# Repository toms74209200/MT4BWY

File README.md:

# May the 4 be with you
[4 Pack](https://www.40percent.club/2017/07/4-pack.html) like 4 key macropad

- 4 key macro keyboard
- Cherry MX/Kailh Choc/Kailh Choc V2 key switch compatible
- USB type-C interface
- On-Board CPU(ATmega32U4)

## Reference

This keyboard is inspired by "4 pack".

[Misc/4pack at master · di0ib/Misc](https://github.com/di0ib/Misc/tree/master/4pack)  
https://github.com/di0ib/Misc/tree/master/4pack

[40% Keyboards: 4 Pack](https://www.40percent.club/2017/07/4-pack.html)  
https://www.40percent.club/2017/07/4-pack.html

## License

MIT License

## Author

[toms74209200](<https://github.com/toms74209200>)

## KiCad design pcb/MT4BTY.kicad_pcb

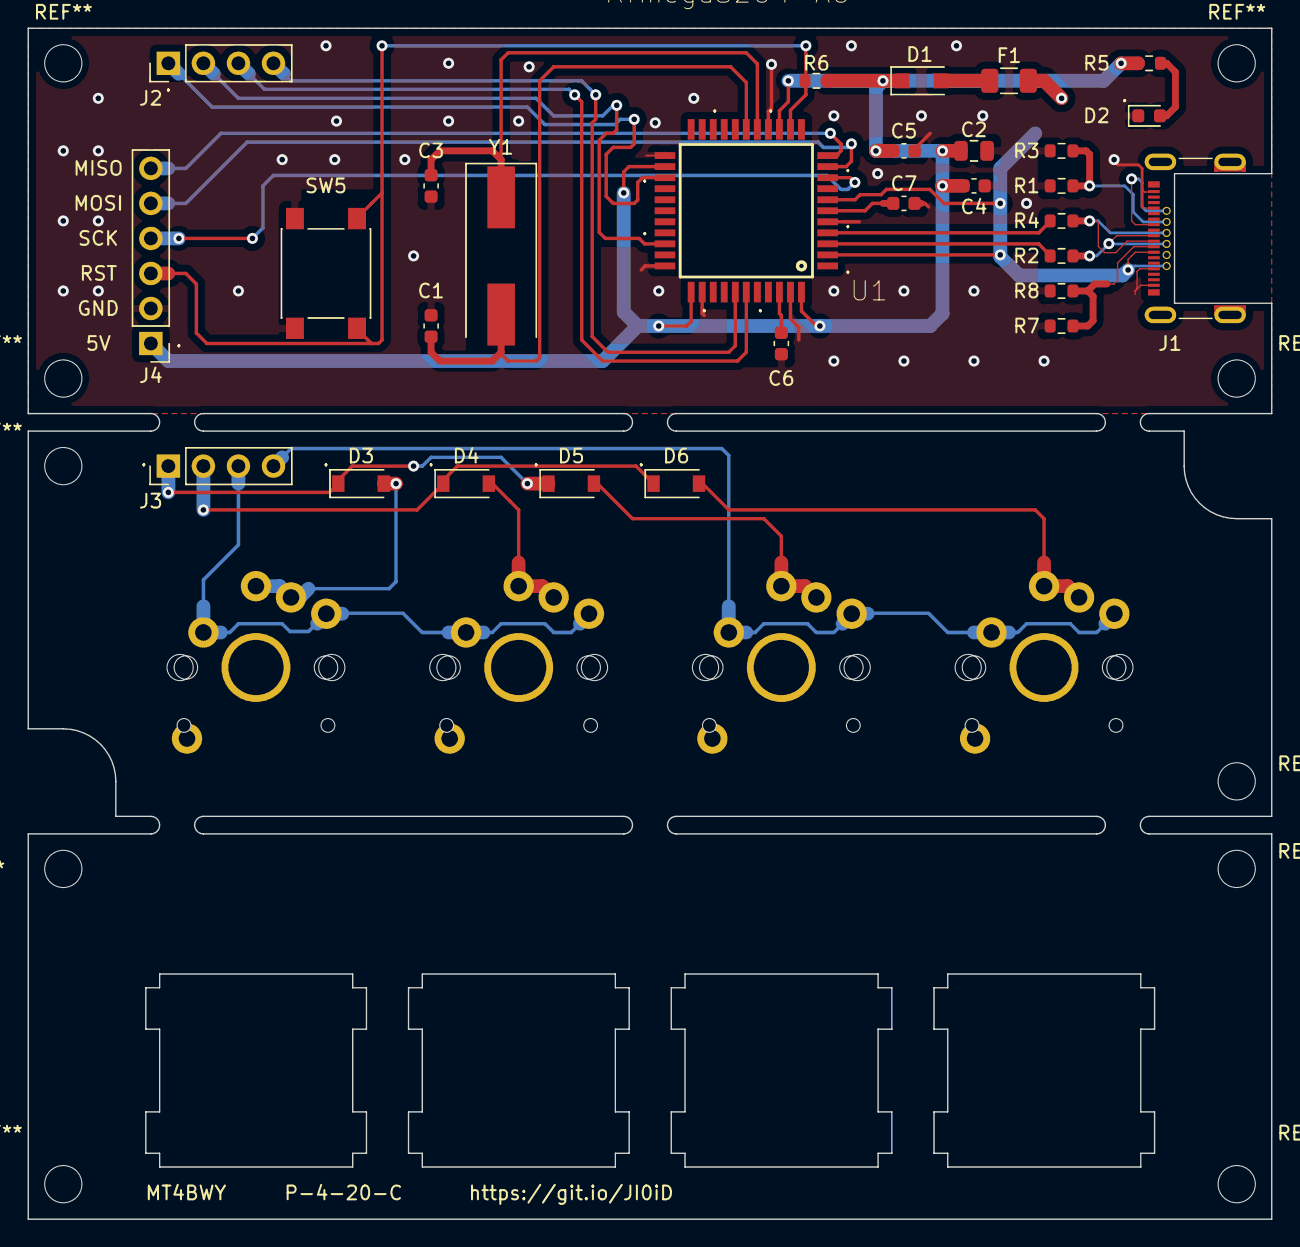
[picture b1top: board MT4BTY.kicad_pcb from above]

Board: 2 copper layers, 90.2 x 86.4 mm, 33 parts (0 on the bottom side), 31 nets.

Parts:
C1, C3: 22p; C_0603_1608Metric
C2: 10u; C_0805_2012Metric
C4, C7: 1u; C_0603_1608Metric
C5, C6: 0.1u; C_0603_1608Metric
D1: RB161MM-20; D_SOD-123F
D2: SMLE13WBC8W1; LED_0603_1608Metric
D3, D4, D5, D6: 1N4148W; D_SOD-123
F1: NANOSMDC050F/13.2; Fuse_1206_3216Metric
J1: CX70M-24P1; USB-C_Female_CX70M-24P1
J2, J3: Conn_01x04_Male; PinHeader_1x04_P2.54mm_Vertical
J4: Conn_01x06_Female; PinHeader_1x06_P2.54mm_Vertical
R1, R3, R5, R6, R7, R8: 10k; R_0603_1608Metric
R2, R4: 22; R_0603_1608Metric
SW1, SW2, SW3, SW4: SW_Push; CherryMX_Choc_V2_1u
SW5: SW_Push; SW_SPST_PTS645
U1: ATmega32U4-AU; ATMEGA32U4-AU
Y1: 16MHz; Crystal_SMD_HC49-SD

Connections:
+5V: C2.1, C4.1, C5.1, D1.1, J4.1, R5.1, R6.1, U1.14, U1.24, U1.34, U1.44
/A2: J2.4, U1.38
/A3: J2.3, U1.39
/CPU_ROW0: J2.1, U1.25
/CPU_ROW1: J2.2, U1.31
/D+: R4.1, U1.4
/D-: R2.1, U1.3
/MISO: J4.6, U1.11
/MOSI: J4.5, U1.10
/RESET: J4.3, R6.2, SW5.2, U1.13
/SCK: J4.4, U1.9
/col0: J3.3, SW1.1, SW2.1
/col1: J3.4, SW3.1, SW4.1
/row0: D3.1, D5.1, J3.1
/row1: D4.1, D6.1, J3.2
GNDPWR: C1.2, C2.2, C3.2, C4.2, C5.2, C6.2, C7.2, D2.1, J1.A1, J1.A12, J1.B1, J1.B12, J4.2, R1.2, R3.2, R7.2, R8.2, SW5.1, U1.5, U1.15, U1.23, U1.33, U1.35, U1.43
unnamed: C1.1, U1.17, Y1.2
unnamed: C3.1, U1.16, Y1.1
unnamed: C6.1, U1.42
unnamed: C7.1, U1.6
unnamed: D1.2, F1.1
unnamed: D2.2, R5.2
unnamed: D3.2, SW1.2
unnamed: D4.2, SW2.2
unnamed: D5.2, SW3.2
unnamed: D6.2, SW4.2
unnamed: J1.A5, R7.1, R8.1
unnamed: J1.A6, J1.B6, R4.2
unnamed: J1.A7, J1.B7, R2.2
unnamed: J1.B5, R1.1, R3.1
VCC: F1.2, J1.A4, J1.A9, J1.B4, J1.B9, U1.2, U1.7

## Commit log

2020-12-08 [add]add schematic first
2020-12-08 [add]add PCB CAD
2020-12-08 [docs]add README
2020-12-26 [fix]fix signal path
